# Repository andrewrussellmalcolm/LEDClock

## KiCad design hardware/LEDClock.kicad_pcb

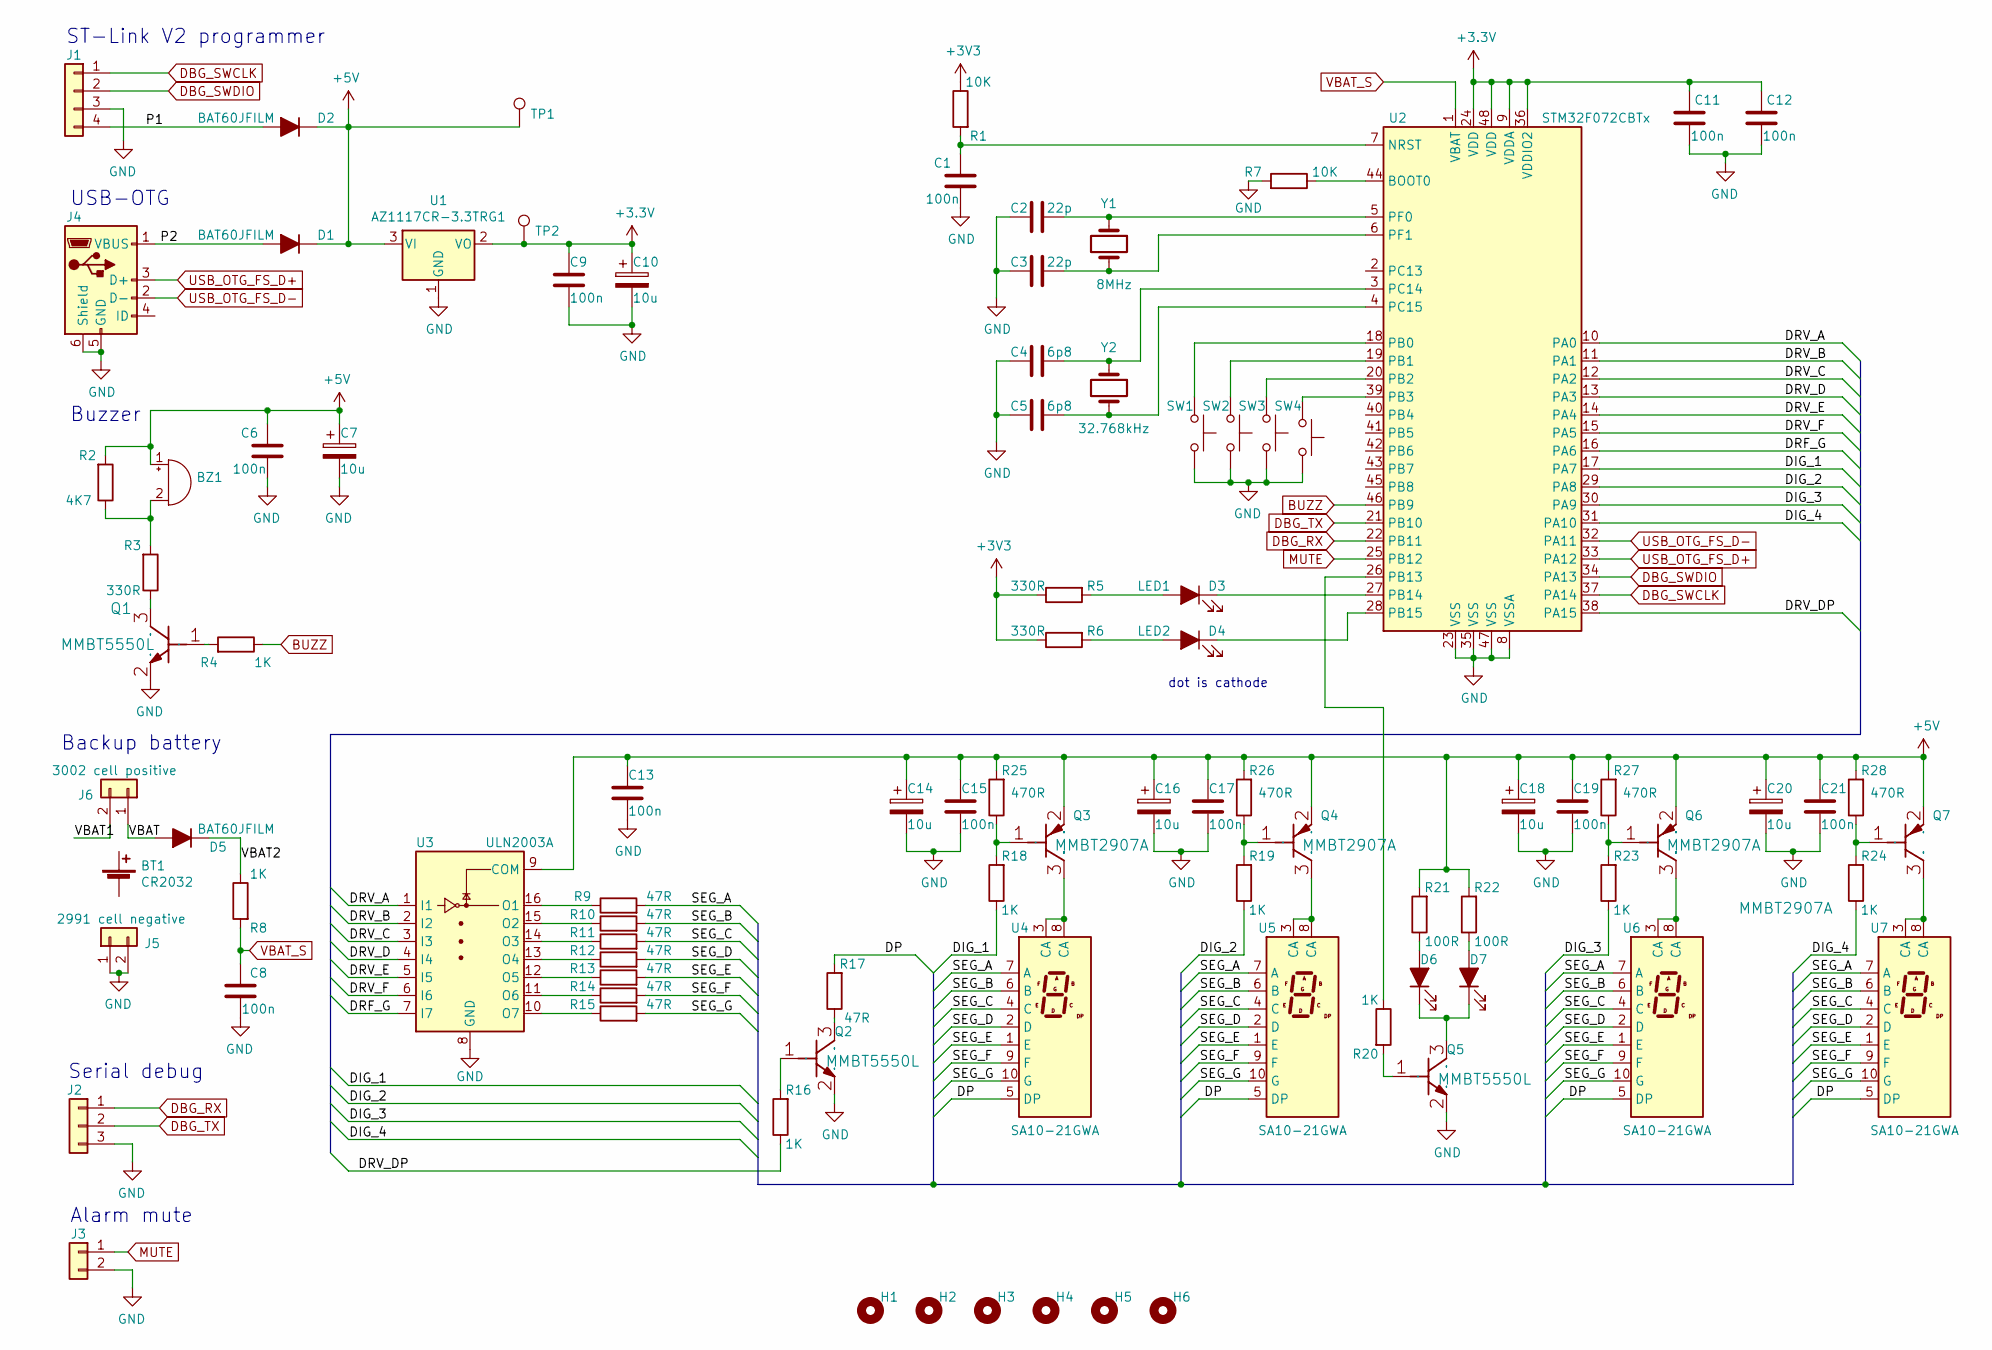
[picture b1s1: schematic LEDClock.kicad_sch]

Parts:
BT1: CR2032; dummy
BZ1: Buzzer; Buzzer_Murata_PKLCS1212E4001-R1; PartNo PKLCS1212E2000
C1, C8, C11, C12: 100n; C_0603_1608Metric; PartNo C0603C104K3RACTU
C2, C3: 22p; C_0603_1608Metric; PartNo C0603C220J5GACTU
C4, C5: 6p8; C_0603_1608Metric; PartNo C0603C689C5GACTU
C6: 100n; C_0603_1608Metric; Voltage 50V; PartNo C0603C104K4RACTU
C7, C10, C14, C16, C18, C20: 10u; CP_EIA-3216-10_Kemet-I; Voltage 6V3; PartNo TAJR106K006RNJ
C9, C13, C15, C17, C19, C21: 100n; C_0603_1608Metric; Voltage 50V; PartNo C0603C104K3RACTU
D1, D2, D5: BAT60JFILM; D_SOD-323; PartNo BAT60JFILM
D3: LED1; LED_0603_1608Metric; PartNo LS Q976
D4: LED2; LED_0603_1608Metric; PartNo LB Q39E-L2OO-35-1
D6, D7: LED_ALT; LED_D4.0mm; PartNo L-424GDT
H1, H2, H3, H4, H5, H6: MountingHole; MountingHole_3.2mm_M3_ISO7380
J1: Conn_01x04; Molex_KK-254_AE-6410-04A_1x04_P2.54mm_Vertical
J2: Conn_01x03; Molex_KK-254_AE-6410-03A_1x03_P2.54mm_Vertical; PartNo 22-27-2031
J3: Conn_01x02; Molex_KK-254_AE-6410-02A_1x02_P2.54mm_Vertical
J4: USB_B_Micro; USB_Micro-B_Molex-105133-0001
J5: 2991 cell negative; SM_BATTERY_2991_(KEYSTONE)_1; PartNo 2991TR
J6: 3002 cell positive; SM_BATTERY_3002_(KEYSTONE)_1; PartNo 3002TR
Q1: MMBT5550L; SOT-23; PartNo MMBT5550LG
Q2, Q5: MMBT5550L; SOT-23; PartNo MMBT5550L
Q3, Q4, Q6, Q7: MMBT2907A; SOT-23; PartNo MMBT2907A
R1, R7: 10K; R_0603_1608Metric; PartNo CRG0603F10K
R2: 4K7; R_0603_1608Metric; PartNo CRG0603F4K7
R3, R5, R6: 330R; R_0603_1608Metric; PartNo CRG0603F330R
R4: 1K; R_0603_1608Metric; PartNo CRG0603F10K
R8: 1K; R_0603_1608Metric; PartNo CRG0603F1K
R9, R10, R11, R12, R13, R14, R15, R17: 47R; R_0603_1608Metric
R16, R18, R19, R20, R23, R24: 1K; R_0603_1608Metric
R21, R22: 100R; R_0603_1608Metric
R25, R26, R27, R28: 470R; R_0603_1608Metric
SW1, SW2, SW3, SW4: SW_Push; SW_PUSH_6mm_H5mm
TP1, TP2: TestPoint-Connector; TestPoint_Pad_D1.0mm
U1: AZ1117CR-3.3TRG1; SOT-89-3
U2: STM32F072CBTx; LQFP-48_7x7mm_P0.5mm
U3: ULN2003A; SO-16_3.9x9.9mm_P1.27mm
U4, U5, U6, U7: SA10-21GWA; SA10-21xxx
Y1: 8MHz; Crystal_SMD_5032-2Pin_5.0x3.2mm; PartNo 144-5033
Y2: 32.768kHz; Crystal_SMD_2012-2Pin_2.0x1.2mm; PartNo X1A000061000212

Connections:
+5V: BZ1.1 (-), C6.2, C7.1, C13.1, C14.1, C15.1, C16.1, C17.1, C18.1, C19.1, C20.1, C21.1, D1.1 (K), D2.1 (K), Q3.2 (EMITTER), Q4.2 (EMITTER), Q6.2 (EMITTER), Q7.2 (EMITTER), R2.2, R21.2, R22.2, R25.2, R26.2, R27.2, R28.2, TP1.1, U1.3 (VI), U3.9 (COM)
/DIG_1: R18.1, U2.17 (PA7)
/DIG_2: R19.1, U2.29 (PA8)
/DIG_3: R23.1, U2.30 (PA9)
/DIG_4: R24.1, U2.31 (PA10)
/DP: R17.2, U4.5 (DP), U5.5 (DP), U6.5 (DP), U7.5 (DP)
/P1: D2.2 (A), J1.4
/P2: D1.2 (A), J4.1 (VBUS)
/SEG_A: R9.2, U4.7 (A), U5.7 (A), U6.7 (A), U7.7 (A)
/SEG_B: R10.2, U4.6 (B), U5.6 (B), U6.6 (B), U7.6 (B)
/SEG_C: R11.2, U4.4 (C), U5.4 (C), U6.4 (C), U7.4 (C)
/SEG_D: R12.2, U4.2 (D), U5.2 (D), U6.2 (D), U7.2 (D)
/SEG_E: R13.2, U4.1 (E), U5.1 (E), U6.1 (E), U7.1 (E)
/SEG_F: R14.2, U4.9 (F), U5.9 (F), U6.9 (F), U7.9 (F)
/SEG_G: R15.2, U4.10 (G), U5.10 (G), U6.10 (G), U7.10 (G)
/VBAT: D5.2 (A), J6.1
/VBAT1: J6.2
/VBAT2: D5.1 (K), R8.1
BUZZ: R4.1, U2.46 (PB9)
DBG_RX: J2.1, U2.22 (PB11)
DBG_SWCLK: J1.1, U2.37 (PA14)
DBG_SWDIO: J1.2, U2.34 (PA13)
DBG_TX: J2.2, U2.21 (PB10)
GND: C1.1, C2.2, C3.2, C4.2, C5.2, C6.1, C7.2, C8.1, C9.2, C10.2, C11.1, C12.1, C13.2, C14.2, C15.2, C16.2, C17.2, C18.2, C19.2, C20.2, C21.2, J1.3, J2.3, J3.2, J4.5 (GND), J4.6 (Shield), J5.1, J5.2, Q1.2 (EMITTER), Q2.2 (EMITTER), Q5.2 (EMITTER), R7.2, SW1.1, SW2.1, SW3.1, SW4.1, U1.1 (GND), U2.8 (VSSA), U2.23 (VSS), U2.35 (VSS), U2.47 (VSS), U3.8 (GND)
MUTE: J3.1, U2.25 (PB12)
unnamed: BZ1.2 (+), R2.1, R3.2
unnamed: C1.2, R1.2, U2.7 (NRST)
unnamed: C2.1, U2.5 (PF0), Y1.1
unnamed: C3.1, U2.6 (PF1), Y1.2
unnamed: C4.1, U2.3 (PC14), Y2.1
unnamed: C5.1, U2.4 (PC15), Y2.2
unnamed: C8.2, R8.2, U2.1 (VBAT)
unnamed: D3.1 (K), U2.27 (PB14)
unnamed: D3.2 (A), R5.2
unnamed: D4.1 (K), U2.28 (PB15)
unnamed: D4.2 (A), R6.2
unnamed: D6.1 (K), D7.1 (K), Q5.3 (COLLECTOR)
unnamed: D6.2 (A), R21.1
unnamed: D7.2 (A), R22.1
unnamed: Q1.1 (BASE), R4.2
unnamed: Q1.3 (COLLECTOR), R3.1
unnamed: Q2.1 (BASE), R16.2
unnamed: Q2.3 (COLLECTOR), R17.1
unnamed: Q3.1 (BASE), R18.2, R25.1
unnamed: Q3.3 (COLLECTOR), U4.3 (CA), U4.8 (CA)
unnamed: Q4.1 (BASE), R19.2, R26.1
unnamed: Q4.3 (COLLECTOR), U5.3 (CA), U5.8 (CA)
unnamed: Q5.1 (BASE), R20.2
unnamed: Q6.1 (BASE), R23.2, R27.1
unnamed: Q6.3 (COLLECTOR), U6.3 (CA), U6.8 (CA)
unnamed: Q7.1 (BASE), R24.2, R28.1
unnamed: Q7.3 (COLLECTOR), U7.3 (CA), U7.8 (CA)
unnamed: R7.1, U2.44 (BOOT0)
unnamed: R9.1, U3.16 (O1)
unnamed: R10.1, U3.15 (O2)
unnamed: R11.1, U3.14 (O3)
unnamed: R12.1, U3.13 (O4)
unnamed: R13.1, U3.12 (O5)
unnamed: R14.1, U3.11 (O6)
unnamed: R15.1, U3.10 (O7)
unnamed: SW1.2, U2.18 (PB0)
unnamed: SW2.2, U2.19 (PB1)
unnamed: SW3.2, U2.20 (PB2)
unnamed: SW4.2, U2.39 (PB3)
unnamed: U2.10 (PA0), U3.1 (I1)
unnamed: U2.11 (PA1), U3.2 (I2)
unnamed: U2.12 (PA2), U3.3 (I3)
unnamed: U2.13 (PA3), U3.4 (I4)
unnamed: U2.14 (PA4), U3.5 (I5)
unnamed: U2.15 (PA5), U3.6 (I6)
unnamed: U2.16 (PA6), U3.7 (I7)
USB_OTG_FS_D+: J4.3 (D+), U2.33 (PA12)
USB_OTG_FS_D-: J4.2 (D-), U2.32 (PA11)

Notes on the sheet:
Backup battery
Alarm mute
Buzzer
USB-OTG
ST-Link V2 programmer
dot is cathode
Serial debug

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
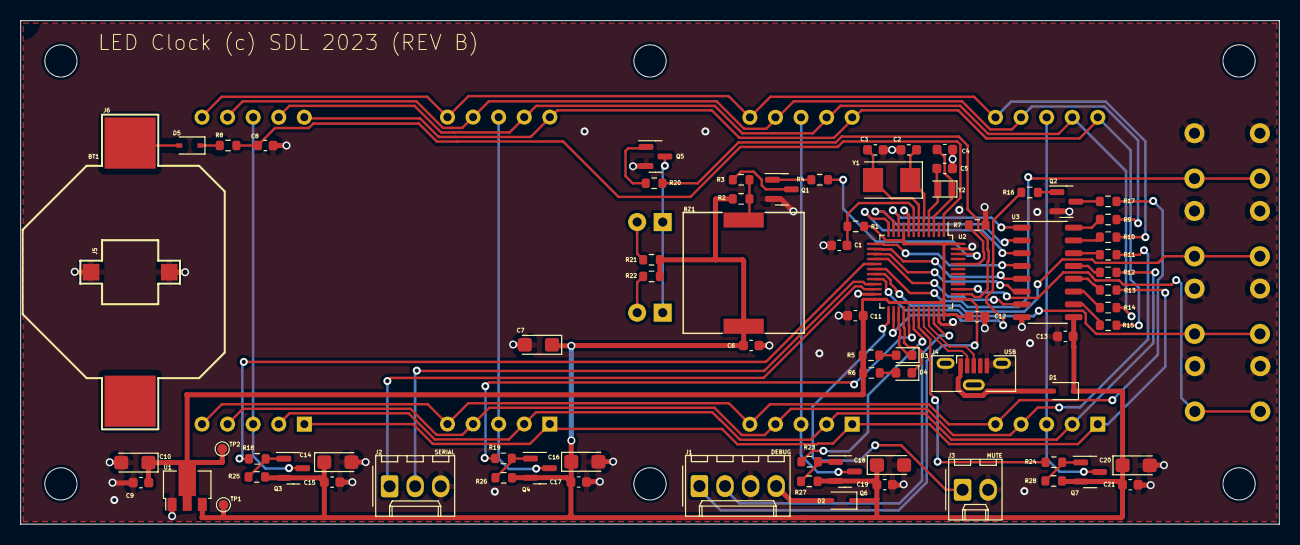
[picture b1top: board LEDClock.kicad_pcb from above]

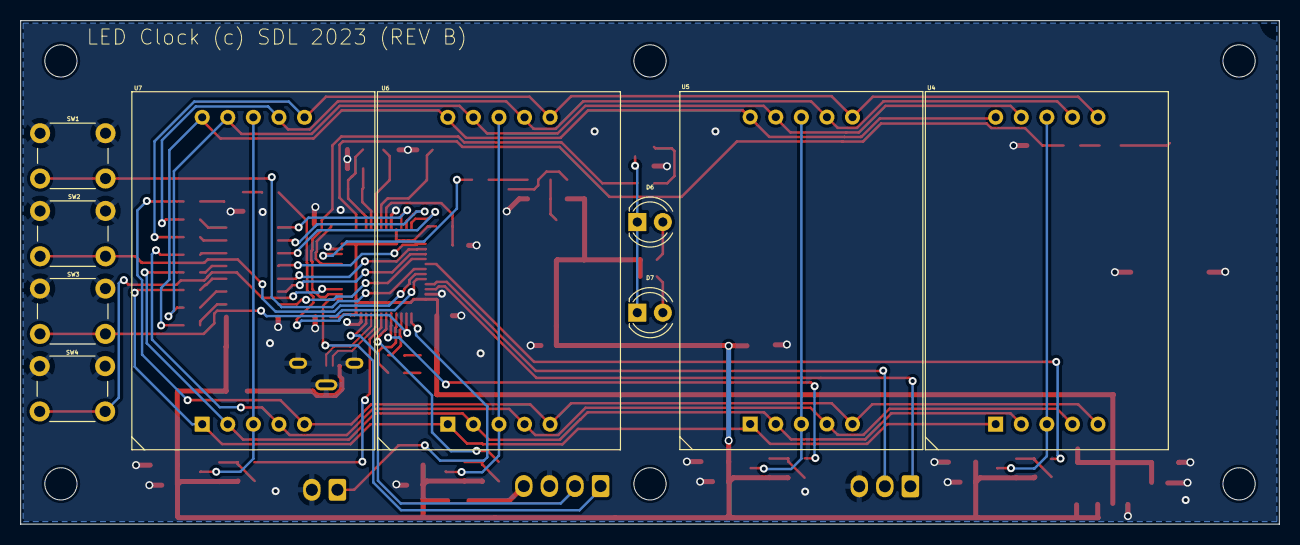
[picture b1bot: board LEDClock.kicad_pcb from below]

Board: 2 copper layers, 125.0 x 50.0 mm, 92 parts (10 on the bottom side), 75 nets.

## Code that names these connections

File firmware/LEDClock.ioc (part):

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Mcu.Name=STM32F072C(8-B)Tx
Mcu.Package=LQFP48
Mcu.UserName=STM32F072CBTx
PA0.GPIOParameters=GPIO_Label
PA0.GPIO_Label=SEG_A
PA0.Signal=GPIO_Output
PA1.GPIOParameters=GPIO_Label
PA1.GPIO_Label=SEG_B
PA1.Signal=GPIO_Output
PA10.GPIOParameters=PinState,GPIO_PuPd,GPIO_Label,GPIO_ModeDefaultOutputPP
PA10.GPIO_Label=DIG_4
PA10.GPIO_ModeDefaultOutputPP=GPIO_MODE_OUTPUT_OD
PA10.GPIO_PuPd=GPIO_NOPULL
PA10.PinState=GPIO_PIN_SET
PA10.Signal=GPIO_Output
PA11.Mode=Device
PA11.Signal=USB_DM
PA12.Mode=Device
PA12.Signal=USB_DP
PA13.Mode=Serial_Wire
PA13.Signal=SYS_SWDIO
PA14.Mode=Serial_Wire
PA14.Signal=SYS_SWCLK
PA15.GPIOParameters=GPIO_Label
PA15.GPIO_Label=COLON
PA15.Signal=GPIO_Output
PA2.GPIOParameters=GPIO_Label
PA2.GPIO_Label=SEG_C
PA2.Signal=GPIO_Output
PA3.GPIOParameters=GPIO_Label
PA3.GPIO_Label=SEG_D
PA3.Signal=GPIO_Output
PA4.GPIOParameters=GPIO_Label
PA4.GPIO_Label=SEG_E
PA4.Signal=GPIO_Output
PA5.GPIOParameters=GPIO_Label
PA5.GPIO_Label=SEG_F
PA5.Signal=GPIO_Output
PA6.GPIOParameters=GPIO_Label
PA6.GPIO_Label=SEG_G
PA6.Signal=GPIO_Output
PA7.GPIOParameters=PinState,GPIO_PuPd,GPIO_Label,GPIO_ModeDefaultOutputPP
PA7.GPIO_Label=DIG_1
PA7.GPIO_ModeDefaultOutputPP=GPIO_MODE_OUTPUT_OD
PA7.GPIO_PuPd=GPIO_NOPULL
PA7.PinState=GPIO_PIN_SET
PA7.Signal=GPIO_Output
PA8.GPIOParameters=GPIO_Speed,PinState,GPIO_PuPd,GPIO_Label,GPIO_ModeDefaultOutputPP
PA8.GPIO_Label=DIG_2
PA8.GPIO_ModeDefaultOutputPP=GPIO_MODE_OUTPUT_OD
PA8.GPIO_PuPd=GPIO_NOPULL
PA8.GPIO_Speed=GPIO_SPEED_FREQ_LOW
PA8.PinState=GPIO_PIN_SET
PA8.Signal=GPIO_Output
PA9.GPIOParameters=PinState,GPIO_PuPd,GPIO_Label,GPIO_ModeDefaultOutputPP
PA9.GPIO_Label=DIG_3
PA9.GPIO_ModeDefaultOutputPP=GPIO_MODE_OUTPUT_OD
PA9.GPIO_PuPd=GPIO_NOPULL
PA9.PinState=GPIO_PIN_SET
PA9.Signal=GPIO_Output
PB0.GPIOParameters=GPIO_PuPd,GPIO_Label,GPIO_ModeDefaultEXTI
PB0.GPIO_Label=SW1_INT
PB0.GPIO_ModeDefaultEXTI=GPIO_MODE_IT_FALLING
PB0.GPIO_PuPd=GPIO_PULLUP
PB0.Signal=GPXTI0
PB1.GPIOParameters=GPIO_PuPd,GPIO_Label,GPIO_ModeDefaultEXTI
PB1.GPIO_Label=SW2_INT
PB1.GPIO_ModeDefaultEXTI=GPIO_MODE_IT_FALLING
PB1.GPIO_PuPd=GPIO_PULLUP
PB1.Signal=GPXTI1
PB10.GPIOParameters=GPIO_Label
PB10.GPIO_Label=DBG_TX
PB10.Mode=Asynchronous
PB10.Signal=USART3_TX
PB11.GPIOParameters=GPIO_Label
PB11.GPIO_Label=DBG_RX
PB11.Mode=Asynchronous
PB11.Signal=USART3_RX
PB12.GPIOParameters=GPIO_PuPd,GPIO_Label,GPIO_ModeDefaultEXTI
PB12.GPIO_Label=SW5_INT
PB12.GPIO_ModeDefaultEXTI=GPIO_MODE_IT_RISING_FALLING
PB12.GPIO_PuPd=GPIO_PULLUP
PB12.Signal=GPXTI12
PB13.GPIOParameters=GPIO_Label
PB13.GPIO_Label=DP
PB13.Signal=GPIO_Output
PB14.GPIOParameters=PinState,GPIO_Label
PB14.GPIO_Label=LED1
PB14.PinState=GPIO_PIN_SET
PB14.Signal=GPIO_Output
PB15.GPIOParameters=PinState,GPIO_Label
PB15.GPIO_Label=LED2
PB15.PinState=GPIO_PIN_SET
PB15.Signal=GPIO_Output
PB2.GPIOParameters=GPIO_PuPd,GPIO_Label,GPIO_ModeDefaultEXTI
PB2.GPIO_Label=SW3_INT
PB2.GPIO_ModeDefaultEXTI=GPIO_MODE_IT_FALLING
PB2.GPIO_PuPd=GPIO_PULLUP
PB2.Signal=GPXTI2
PB3.GPIOParameters=GPIO_PuPd,GPIO_Label,GPIO_ModeDefaultEXTI
PB3.GPIO_Label=SW4_INT
PB3.GPIO_ModeDefaultEXTI=GPIO_MODE_IT_FALLING
PB3.GPIO_PuPd=GPIO_PULLUP
PB3.Signal=GPXTI3
PB9.GPIOParameters=GPIO_Label
PB9.GPIO_Label=BUZZER
PB9.Signal=GPIO_Output
PC14-OSC32_IN.Mode=LSE-External-Oscillator
PC14-OSC32_IN.Signal=RCC_OSC32_IN
PC15-OSC32_OUT.Mode=LSE-External-Oscillator
PC15-OSC32_OUT.Signal=RCC_OSC32_OUT
PF0-OSC_IN.Mode=HSE-External-Oscillator
PF0-OSC_IN.Signal=RCC_OSC_IN
PF1-OSC_OUT.Mode=HSE-External-Oscillator
PF1-OSC_OUT.Signal=RCC_OSC_OUT
RCC.SYSCLKFreq_VALUE=48000000
RCC.SYSCLKSource=RCC_SYSCLKSOURCE_PLLCLK
board=custom
